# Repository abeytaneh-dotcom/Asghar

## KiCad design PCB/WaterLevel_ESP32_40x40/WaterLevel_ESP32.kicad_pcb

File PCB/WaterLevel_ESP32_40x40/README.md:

# Water Level Ethernet Controller — 40×40 mm Rev A

دو لایه، 1.6 mm FR-4. این پروژه برای کنترل/اندازه‌گیری 4 سطح آب با ESP32-C3 SuperMini و ارتباط Ethernet ساخته شده است.

## معماری
- MCU module: ESP32-C3 SuperMini, 2×8, 2.54 mm pitch, 15.24 mm row spacing
- Ethernet: WIZnet W5500 + 25 MHz crystal + HR911105A integrated-magnetics RJ45
- Power: 7–24 V nominal input -> MP1584EN -> 3.3 V
- Water probes: COM + L1/L2/L3/L4
- Excitation: AO3401A P-MOS controlled by GPIO8, normally OFF
- Sense: 4× MMBT3904 stages, active-low into ESP32
- PCB: 40.0 × 40.0 mm, 2 copper layers

## ESP32 pin map
| Function | GPIO |
|---|---:|
| W5500 MISO | 5 |
| W5500 SCLK | 6 |
| W5500 MOSI | 7 |
| W5500 CS | 10 |
| W5500 RESET | 4 |
| W5500 INT | 3 |
| Probe excitation | 8 |
| Level 1 | 0 |
| Level 2 | 1 |
| Level 3 | 20 |
| Level 4 | 21 |

## Probe logic
GPIO8 is held high by the external gate pull-up, so the common electrode is OFF at reset. Firmware should briefly drive GPIO8 LOW, wait a few milliseconds, sample LEVEL1..LEVEL4, then drive GPIO8 HIGH again. This avoids continuous DC excitation of the water electrodes.

## Network
The W5500 SPI control signals are routed to the ESP32. MDI routing uses short differential paths to the HR911105A and follows the W5500 reference network (TX 51R bias, TCT 10R/22nF, RX 6.8nF AC coupling with 82R bias to RCT).

## Power
The MP1584EN stage follows the 3.3 V application values: 10 uH, 124 k / 40.2 k feedback divider, 22 uF output, 100 nF bootstrap. Do not connect the ESP32 USB 5 V and an external 5 V source simultaneously; this board powers the module through its 3V3 rail.

## Files
- `WaterLevel_ESP32.kicad_pcb` — routed board source
- `WaterLevel_ESP32.kicad_sch` — project overview sheet
- `WaterLevel_ESP32.kicad_pro` — KiCad project
- `BOM.csv` — component list
- `NETLIST.md` — electrical connectivity / design notes

## Before manufacturing
Run KiCad DRC after opening the project and refill copper zones. Verify the exact purchased HR911105A mechanical drawing before ordering PCBs because clone jacks can differ in shield-pin geometry.

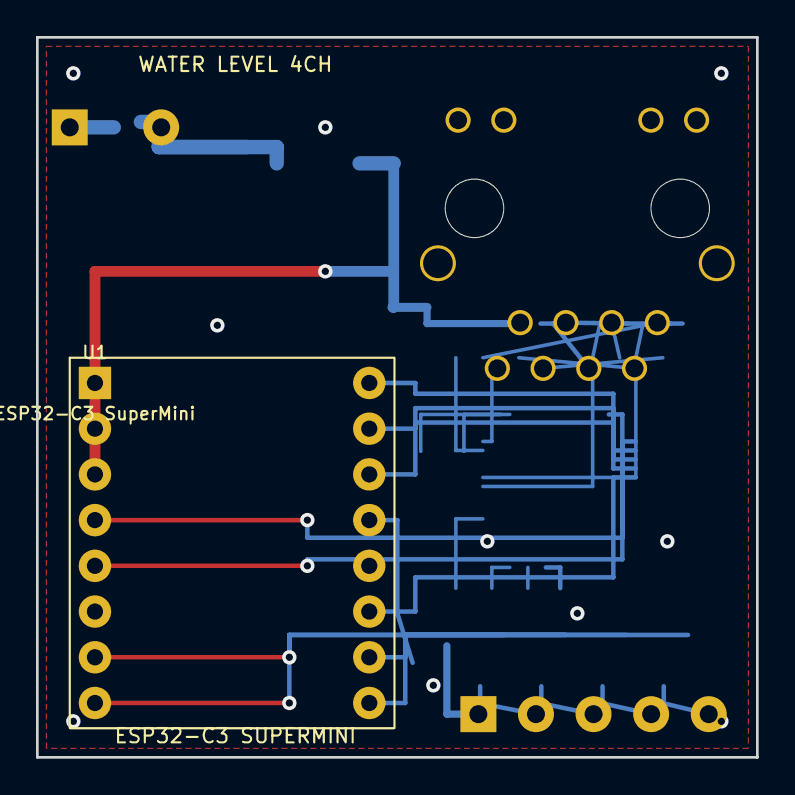
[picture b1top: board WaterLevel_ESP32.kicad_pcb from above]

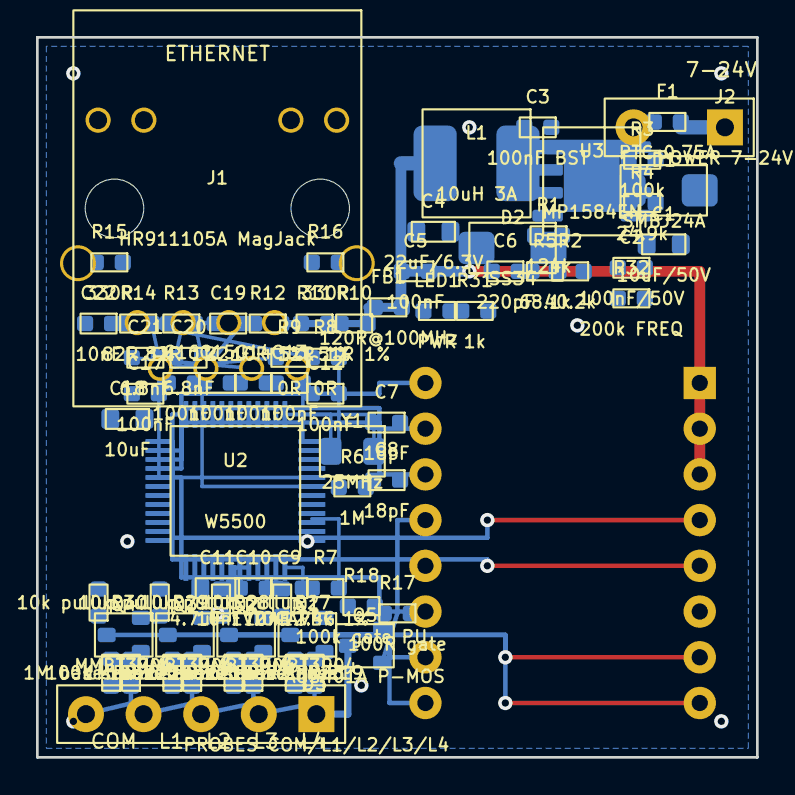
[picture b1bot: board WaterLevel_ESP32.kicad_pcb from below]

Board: 2 copper layers, 40.0 x 40.0 mm, 72 parts (71 on the bottom side), 51 nets.

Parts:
C1: 10uF/50V; C_0805
C2: 100nF/50V; C_0603
C3: 100nF BST; C_0603
C4: 22uF/6.3V; C_0805
C5, C12, C13, C14, C15, C16, C17: 100nF; C_0603
C6: 220pF; C_0603
C7, C8: 18pF; C_0603
C9: 10nF VBG; C_0603
C10: 10nF TOCAP; C_0603
C11: 4.7uF 1V2; C_0805
C18: 10uF; C_0805
C19: 22nF; C_0603
C20, C21: 6.8nF; C_0603
C22: 10nF; C_0603
D1: SMBJ24A; D_SMA
D2: SS34; D_SMA
F1: PTC 0.75A; R_0603
FB1: 120R@100MHz; R_0603
J1: HR911105A MagJack; HR911105A
J2: POWER 7-24V; Terminal_2
J3: PROBES COM/L1/L2/L3/L4; Terminal_5
L1: 10uH 3A; L_6x6
LED1: PWR; LED_0603
Q1, Q2, Q3, Q4: MMBT3904; SOT-23
Q5: AO3401A P-MOS; SOT-23
R1: 124k; R_0603
R2: 40.2k; R_0603
R3: 100k; R_0603
R4: 24.9k; R_0603
R5: 68.1k; R_0603
R6: 1M; R_0603
R7: 12.4k 1%; R_0603
R8, R9: 0R; R_0603
R10, R11: 51R 1%; R_0603
R12: 10R 1%; R_0603
R13, R14: 82R 1%; R_0603
R15, R16: 330R; R_0603
R17: 100R gate; R_0603
R18: 100k gate PU; R_0603
R19, R20, R21, R22: 100k sense; R_0603
R23, R24, R25, R26: 1M base PD; R_0603
R27, R28, R29, R30: 10k pullup; R_0603
R31: 1k; R_0603
R32: 200k FREQ; R_0603
U1: ESP32-C3 SuperMini; ESP32-C3_SuperMini_Socket
U2: W5500; LQFP-48_7x7_P0.5
U3: MP1584EN; SOIC-8_EP
Y1: 25MHz; Crystal_3225_2Pin

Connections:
3V3A: C12.1, C13.1, C14.1, C15.1, C16.1, FB1.2, R10.1, R11.1, R12.1, U2.4, U2.8, U2.11, U2.15, U2.17, U2.21
3V3D: C4.1, C5.1, C17.1, C18.1, FB1.1, J1.12, L1.2, Q5.2, R1.1, R15.2, R16.2, R18.2, R27.1, R28.1, R29.1, R30.1, R31.1, U1.3, U2.28, U2.43, U2.44, U2.45
ACT_LED: J1.10, R15.1, U2.27
BST: C3.1, U3.8
COMP: R5.1, U3.3
COMP_RC: C6.1, R5.2
EN: R3.2, R4.1, U3.2
ETH_RXN: C21.2, J1.6
ETH_RXP: C20.2, J1.3
ETH_TXN: J1.2, R9.2, R11.2
ETH_TXP: J1.1, R8.2, R10.2
FB: R1.2, R2.1, U3.4
FREQ: R32.1, U3.6
GND: C1.2, C2.2, C4.2, C5.2, C6.2, C7.2, C8.2, C9.2, C10.2, C11.2, C12.2, C13.2, C14.2, C15.2, C16.2, C17.2, C18.2, C19.2, C22.2, D1.2, D2.1, J1.13, J1.14, J2.2, LED1.2, Q1.2, Q2.2, Q3.2, Q4.2, R2.2, R4.2, R7.2, R23.2, R24.2, R25.2, R26.2, R32.2, U1.2, U2.3, U2.9, U2.14, U2.16, U2.19, U2.29, U2.48, U3.5, U3.9
LEVEL1: Q1.3, R27.2, U1.8
LEVEL2: Q2.3, R28.2, U1.7
LEVEL3: Q3.3, R29.2, U1.15
LEVEL4: Q4.3, R30.2, U1.16
LINK_LED: J1.11, R16.1, U2.25
P1_RAW: J3.2, R19.1
P2_RAW: J3.3, R20.1
P3_RAW: J3.4, R21.1
P4_RAW: J3.5, R22.1
PROBE_COM: J3.1, Q5.3
PROBE_EN: Q5.1, R17.1, R17.2, R18.1, U1.12
PWR_LED: LED1.1, R31.2
Q1_BASE: Q1.1, R19.2, R23.1
Q2_BASE: Q2.1, R20.2, R24.1
Q3_BASE: Q3.1, R21.2, R25.1
Q4_BASE: Q4.1, R22.2, R26.1
RCT: C22.1, J1.5, R13.2, R14.2
SW: C3.2, D2.2, L1.1, U3.1
TCT: C19.1, J1.4, R12.2
VIN: C1.1, C2.1, D1.1, F1.2, R3.1, U3.7
VIN_RAW: F1.1, J2.1
W_1V2: C11.1, U2.22
W_CS: U1.14, U2.32
W_EXRES: R7.1, U2.10
W_INT: U1.5, U2.36
W_MISO: U1.9, U2.34
W_MOSI: U1.11, U2.35
W_RST: U1.4, U2.37
W_RXN: C21.1, R14.1, U2.5
W_RXP: C20.1, R13.1, U2.6
W_SCK: U1.10, U2.33
W_TOCAP: C10.1, U2.20
W_TXN: R9.1, U2.1
W_TXP: R8.1, U2.2
W_VBG: C9.1, U2.18
W_XI: C7.1, R6.1, U2.30, Y1.1
W_XO: C8.1, R6.2, U2.31, Y1.2

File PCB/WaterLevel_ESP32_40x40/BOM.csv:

Reference,Value,Package,Qty
U1,ESP32-C3 SuperMini,Module,1
U2,W5500,LQFP-48 7x7 P0.5,1
U3,MP1584EN,SOIC-8EP,1
J1,HR911105A,RJ45 MagJack,1
J2,2-pin power terminal,5.08mm,1
J3,5-pin probe terminal,3.2mm,1
Q1-Q4,MMBT3904,SOT-23,4
Q5,AO3401A,SOT-23,1
Y1,25MHz crystal,3225,1
L1,10uH >=3A,6x6 SMD,1
FB1,Ferrite 120R@100MHz,0603,1
D1,SMBJ24A TVS,SMB,1
D2,SS34 Schottky,SMA,1
F1,PTC 0.75A,0603/1206,1
R1,124k 1%,0603,1
R2,40.2k 1%,0603,1
R3,100k,0603,1
R4,24.9k,0603,1
R5,68.1k,0603,1
R6,1M,0603,1
R7,12.4k 1%,0603,1
R8-R9,0R,0603,2
R10-R11,51R 1%,0603,2
R12,10R 1%,0603,1
R13-R14,82R 1%,0603,2
R15-R16,330R,0603,2
R17,100R,0603,1
R18,100k,0603,1
R19-R22,100k,0603,4
R23-R26,1M,0603,4
R27-R30,10k,0603,4
R31,1k,0603,1
R32,200k FREQ,0603,1
C1,10uF 50V,0805/1206,1
C2,100nF 50V,0603,1
C3,100nF bootstrap,0603,1
C4,22uF 6.3V,0805,1
C5,100nF,0603,1
C6,220pF,0603,1
C7-C8,18pF,0603,2
C9-C10,10nF,0603,2
C11,4.7uF,0805,1
C12-C17,100nF decoupling,0603,6
C18,10uF,0805,1
C19,22nF,0603,1
C20-C21,6.8nF,0603,2
C22,10nF,0603,1
LED1,Power LED,0603,1
